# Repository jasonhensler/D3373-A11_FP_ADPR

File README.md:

# D3373-A11_FP_ADPR
An pin adapter pcb for an Fujitsu D3373-A11 MB Front panel connector to standard 2.54mm pin headers for desktop case connector.

I have not tested v2, but I did adapt the temparature sensor pinouts to mate with an lm75 module with 2.54mm pins.

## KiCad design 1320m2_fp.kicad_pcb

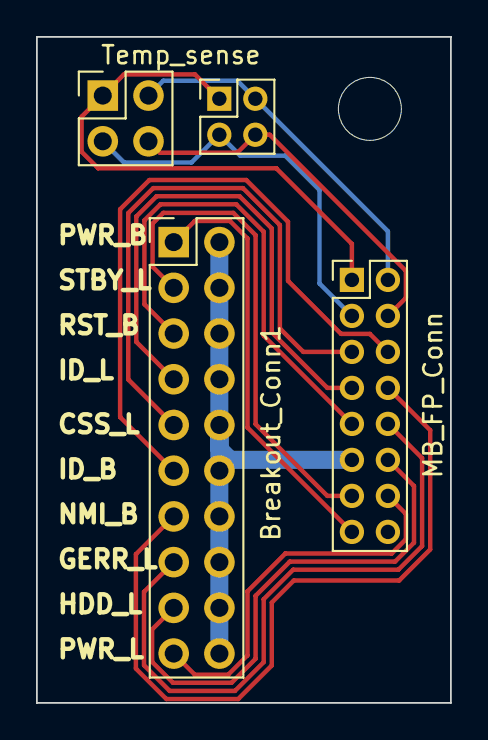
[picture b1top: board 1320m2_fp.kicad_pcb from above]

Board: 2 copper layers, 23.0 x 37.0 mm, 4 parts (0 on the bottom side), 14 nets.

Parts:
Breakout_Conn1: Breakout_Conn; PinHeader_2x10_P2.54mm_Vertical
MB_FP_Conn1: MB_FP_Conn; PinHeader_2x08_P2.00mm_Vertical
Temp_sense: Temp_sense2; PinHeader_2x02_P2.54mm_Vertical
Temp_sense2: Temp_sense; PinHeader_2x02_P2.00mm_Vertical

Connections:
/3.3v: MB_FP_Conn1.2, Temp_sense.2, Temp_sense2.2
/CSS_LED: Breakout_Conn1.9, MB_FP_Conn1.5
/GErr_LED: Breakout_Conn1.15, MB_FP_Conn1.10
/GND: Breakout_Conn1.2, Breakout_Conn1.4, Breakout_Conn1.6, Breakout_Conn1.8, Breakout_Conn1.10, Breakout_Conn1.12, Breakout_Conn1.14, Breakout_Conn1.16, Breakout_Conn1.18, Breakout_Conn1.20, MB_FP_Conn1.3, MB_FP_Conn1.11, Temp_sense.3, Temp_sense2.3
/HDD_LED: Breakout_Conn1.17, MB_FP_Conn1.12
/ID_BTN: Breakout_Conn1.11, MB_FP_Conn1.6
/ID_LED: Breakout_Conn1.7, MB_FP_Conn1.7
/NMI_BTN: Breakout_Conn1.13, MB_FP_Conn1.8
/PWR_BTN: Breakout_Conn1.1, MB_FP_Conn1.15
/PWR_LED: Breakout_Conn1.19, MB_FP_Conn1.14
/Reset_BTN: Breakout_Conn1.5, MB_FP_Conn1.9
/SCL: MB_FP_Conn1.4, Temp_sense.4, Temp_sense2.4
/SDA: MB_FP_Conn1.1, Temp_sense.1, Temp_sense2.1
/Standby_LED: Breakout_Conn1.3, MB_FP_Conn1.13

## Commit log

2023-08-17 Dumping Kicad files
2023-08-17 V2 pinouts to mate with an lm75 module directly.
